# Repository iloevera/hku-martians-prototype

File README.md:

# HKU Martians Prototype Rover

Rudimentary 2-layer all-in-one Power Distribution Board (PDB) and logic carrier designed for small 6-wheel rovers with a 4-DoF robotic arm.

## 🚀 Key Specifications
- **Dimensions:** 99.57 x 99.06 mm
- **Power Input:** 6S LiPo (22.2V nominal, 25.2V max) via XT60.
- **Power Tree:**
  - **12V @ 10.8A:** High-current rail for BLDC/DC Main Drive motors. External module attached through XT30 connectors
  - **7.5V @ 5A:** Dedicated HV Servo rail (Optimized for 7.4V nominal servos). External module attached through XT30 connectors
  - **5.1V @ 5A:** On-board stabilized logic power for Pi 5 and peripherals. 3V3 Using Pico's built-in regulator.
- **Processing:**
  - Dual-core architecture: Raspberry Pi 5 (Thinking) + Pi Pico 2 (Doing).
  - UART communication bridge.
- **Actuation & Sensing:**
  - 6x PWM Encoder inputs.
  - 6x PWM-Controlled DC motor driver headers.
  - 4x High-Torque Servo ports with localized bulk capacitance.
  - Integrated 6S Battery Fuel Gauge (Voltage Divider + ADC).

## 🛠 Hardware Setup
### Battery Monitor Calibration
The internal voltage divider uses a **100kΩ (Top)** and **13.7kΩ (Bottom)** 1% precision resistor set. 
- **Max Input:** 25.2V
- **ADC Output:** ~3.03V
- **Safety Factor:** 10% headroom to prevent Pico ADC overvoltage.

### Communication
The Pi 5 and Pico 2 communicate via UART.
- **Baud Rate:** 115200 (Default)
- **Pinout:** Pi GPIO 14/15 <-> Pico GPIO 0/1.

## ⚠️ Assembly Warnings
1. **Thermal Reliefs:** High-current pads (XT60, Regulators, Motors) have thermal reliefs **DISABLED**. Use a high-power chisel-tip iron and pre-heat the board to 100°C for assembly.
2. **Capacitors:** Ensure C1 & C2 (2000uF) is rated for 50V minimum.
3. **USB Isolation:** Always use a USB isolator when debugging the Pi/Pico while the main battery is connected to prevent back-powering your PC.

## 📜 License
This project is released under CERN-OHL-W-2.0 license. Designed by **Ilo Japar / HKU Martians**.

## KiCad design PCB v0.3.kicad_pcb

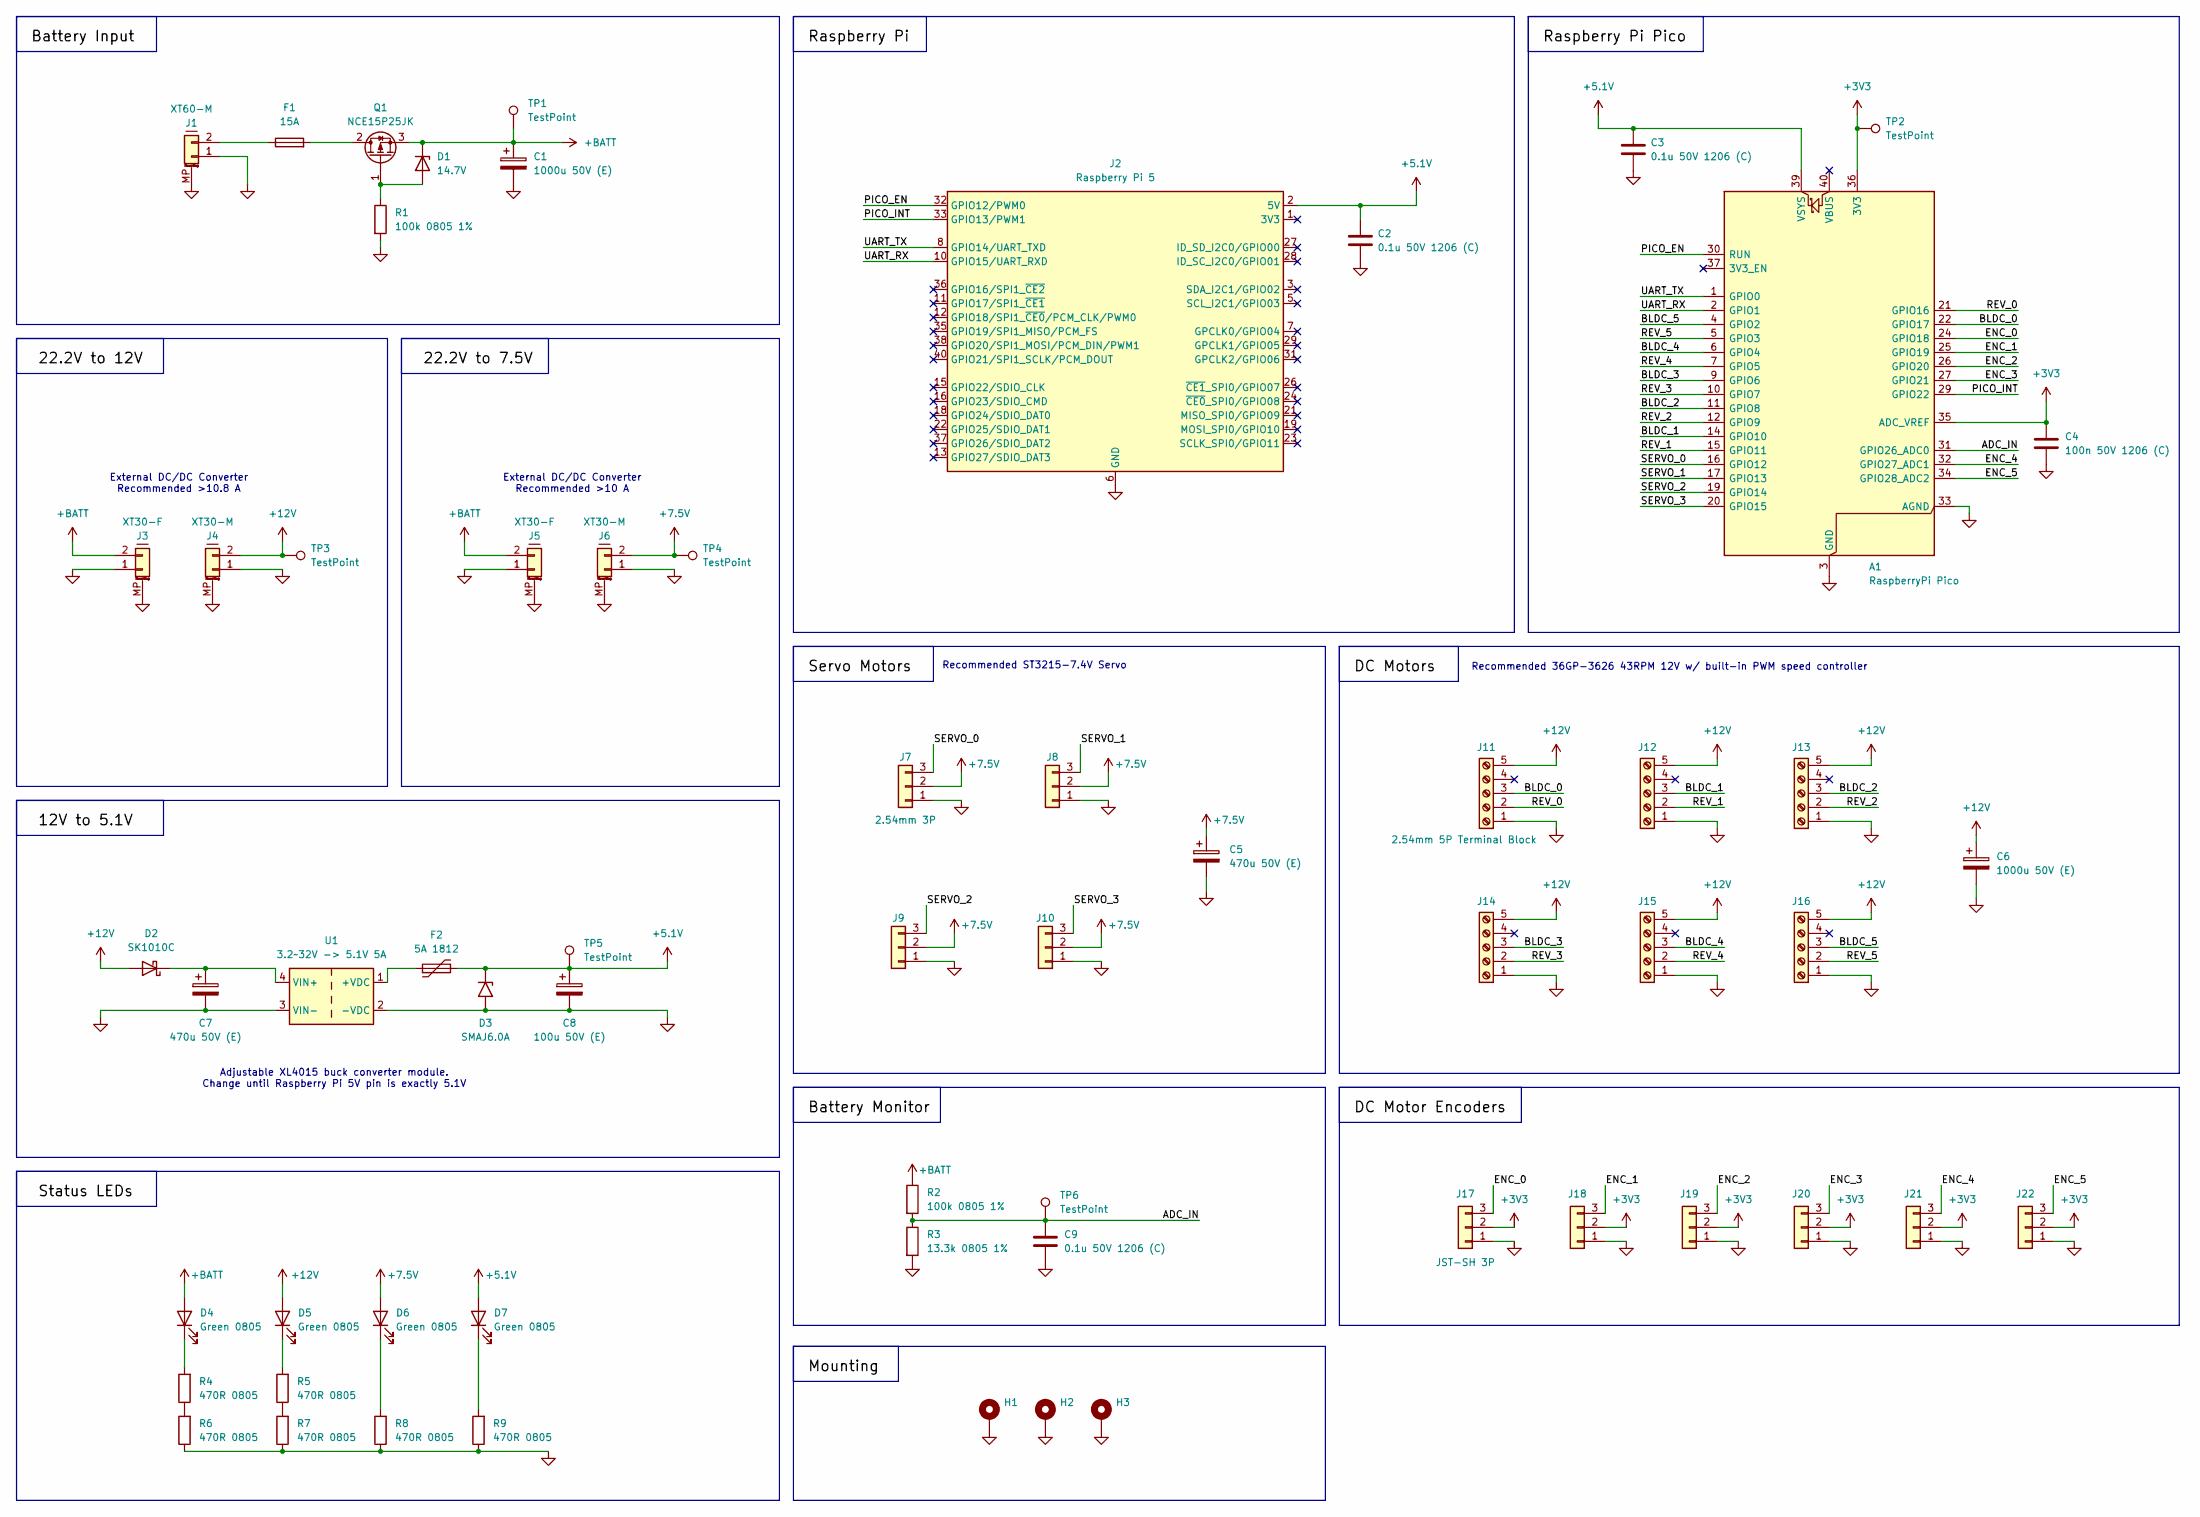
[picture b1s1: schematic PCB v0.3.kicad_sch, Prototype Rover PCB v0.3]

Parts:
A1: RaspberryPi Pico; RaspberryPi_Pico_SMD_HandSolder
C1, C6: 1000u 50V (E); CP_Radial_D13.0mm_P5.00mm
C2, C3, C9: 0.1u 50V 1206 (C); C_1206_3216Metric_Pad1.33x1.80mm_HandSolder
C4: 100n 50V 1206 (C); C_1206_3216Metric_Pad1.33x1.80mm_HandSolder
C5, C7: 470u 50V (E); CP_Radial_D10.0mm_P5.00mm
C8: 100u 50V (E); CP_Radial_D8.0mm_P3.50mm
D1: 14.7V; Nexperia_CFP3_SOD-123W
D2: SK1010C; D_SMC_Handsoldering
D3: SMAJ6.0A; D_SMA
D4, D5, D6, D7: Green 0805; LED_0805_2012Metric_Pad1.15x1.40mm_HandSolder
F1: 15A; Fuse_Blade_ATO_directSolder
F2: 5A 1812; Fuse_1812_4532Metric_Pad1.30x3.40mm_HandSolder
H1, H2, H3: M3 3.2mm; MountingHole_3.2mm_M3_DIN965_Pad
J1: XT60-M; AMASS_XT60PW-M_1x02_P7.20mm_Horizontal
J2: Raspberry Pi 5; raspberrypi_2_3
J3, J5: XT30-F; AMASS_XT30PW-F_1x02_P2.50mm_Horizontal
J4, J6: XT30-M; AMASS_XT30PW-M_1x02_P2.50mm_Horizontal
J7, J8, J9, J10: 2.54mm 3P; PinHeader_1x03_P2.54mm_Vertical
J11, J12, J13, J14, J15, J16: 2.54mm 5P Terminal Block; TerminalBlock_Xinya_XY308-2.54-5P_1x05_P2.54mm_Horizontal
J17, J18, J19, J20, J21, J22: JST-SH 3P; JST_SH_BM03B-SRSS-TB_1x03-1MP_P1.00mm_Vertical
Q1: NCE15P25JK; TO-252-2
R1, R2: 100k 0805 1%; R_0805_2012Metric_Pad1.20x1.40mm_HandSolder
R3: 13.3k 0805 1%; R_0805_2012Metric_Pad1.20x1.40mm_HandSolder
R4, R5, R6, R7, R8, R9: 470R 0805; R_0805_2012Metric_Pad1.20x1.40mm_HandSolder
TP1, TP2, TP3, TP4, TP5, TP6: TestPoint; TestPoint_Pad_D1.5mm
U1: 3.2~32V -> 5.1V 5A; Buck_Converter_54x24mm

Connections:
+3V3: A1.35 (ADC_VREF), A1.36 (3V3), C4.1, J17.2, J18.2, J19.2, J20.2, J21.2, J22.2, TP2.1 (1_1)
+5.1V: A1.39 (VSYS), C2.1, C3.1, C8.1, D3.1 (A1), D7.2 (A), F2.2, J2.2 (5V), J2.4 (5V), TP5.1 (1_1)
+7.5V: C5.1, D6.2 (A), J6.2, J7.2, J8.2, J9.2, J10.2, TP4.1 (1_1)
+12V: C6.1, D2.2 (A), D5.2 (A), J4.2, J11.5, J12.5, J13.5, J14.5, J15.5, J16.5, TP3.1 (1_1)
+BATT: C1.1, D1.1 (K), D4.2 (A), J3.2, J5.2, Q1.3 (S), R2.1, TP1.1 (1_1)
/ADC_IN: A1.31 (GPIO26_ADC0), C9.1, R2.2, R3.1, TP6.1 (1_1)
/BLDC_0: A1.22 (GPIO17), J11.3
/BLDC_1: A1.14 (GPIO10), J12.3
/BLDC_2: A1.11 (GPIO8), J13.3
/BLDC_3: A1.9 (GPIO6), J14.3
/BLDC_4: A1.6 (GPIO4), J15.3
/BLDC_5: A1.4 (GPIO2), J16.3
/ENC_0: A1.24 (GPIO18), J17.3
/ENC_1: A1.25 (GPIO19), J18.3
/ENC_2: A1.26 (GPIO20), J19.3
/ENC_3: A1.27 (GPIO21), J20.3
/ENC_4: A1.32 (GPIO27_ADC1), J21.3
/ENC_5: A1.34 (GPIO28_ADC2), J22.3
/PICO_EN: A1.30 (RUN), J2.32 (GPIO12/PWM0)
/PICO_INT: A1.29 (GPIO22), J2.33 (GPIO13/PWM1)
/REV_0: A1.21 (GPIO16), J11.2
/REV_1: A1.15 (GPIO11), J12.2
/REV_2: A1.12 (GPIO9), J13.2
/REV_3: A1.10 (GPIO7), J14.2
/REV_4: A1.7 (GPIO5), J15.2
/REV_5: A1.5 (GPIO3), J16.2
/SERVO_0: A1.16 (GPIO12), J7.3
/SERVO_1: A1.17 (GPIO13), J8.3
/SERVO_2: A1.19 (GPIO14), J9.3
/SERVO_3: A1.20 (GPIO15), J10.3
/UART_RX: A1.2 (GPIO1), J2.10 (GPIO15/UART_RXD)
/UART_TX: A1.1 (GPIO0), J2.8 (GPIO14/UART_TXD)
GND: A1.3 (GND), A1.8 (GND), A1.13 (GND), A1.18 (GND), A1.23 (GND), A1.28 (GND), A1.33 (AGND), A1.38 (GND), C1.2, C2.2, C3.2, C4.2, C5.2, C6.2, C7.2, C8.2, C9.2, D3.2 (A2), H1.1 (1_1), H2.1 (1_1), H3.1 (1_1), J1.1, J1.MP (MountPin), J2.6 (GND), J2.9 (GND), J2.14 (GND), J2.20 (GND), J2.25 (GND), J2.30 (GND), J2.34 (GND), J2.39 (GND), J3.1, J3.MP (MountPin), J4.1, J4.MP (MountPin), J5.1, J5.MP (MountPin), J6.1, J6.MP (MountPin), J7.1, J8.1, J9.1, J10.1, J11.1, J12.1, J13.1, J14.1, J15.1, J16.1, J17.1, J18.1, J19.1, J20.1, J21.1, J22.1, R1.2, R3.2, R6.1, R7.1, R8.1, R9.1, U1.2 (-VDC), U1.3 (VIN-)
unnamed: D1.2 (A), Q1.1 (G), R1.1
unnamed: C7.1, D2.1 (K), U1.4 (VIN+)
unnamed: D4.1 (K), R4.2
unnamed: D5.1 (K), R5.2
unnamed: D6.1 (K), R8.2
unnamed: D7.1 (K), R9.2
unnamed: F1.1, J1.2
unnamed: F1.2, Q1.2 (D)
unnamed: R4.1, R6.2
unnamed: R5.1, R7.2
unnamed: F2.1, U1.1 (+VDC)

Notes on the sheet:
Adjustable XL4015 buck converter module. Change until Raspberry Pi 5V pin is exactly 5.1V
External DC/DC Converter Recommended >10 A
Recommended 36GP-3626 43RPM 12V w/ built-in PWM speed controller
Recommended ST3215-7.4V Servo
External DC/DC Converter Recommended >10.8 A

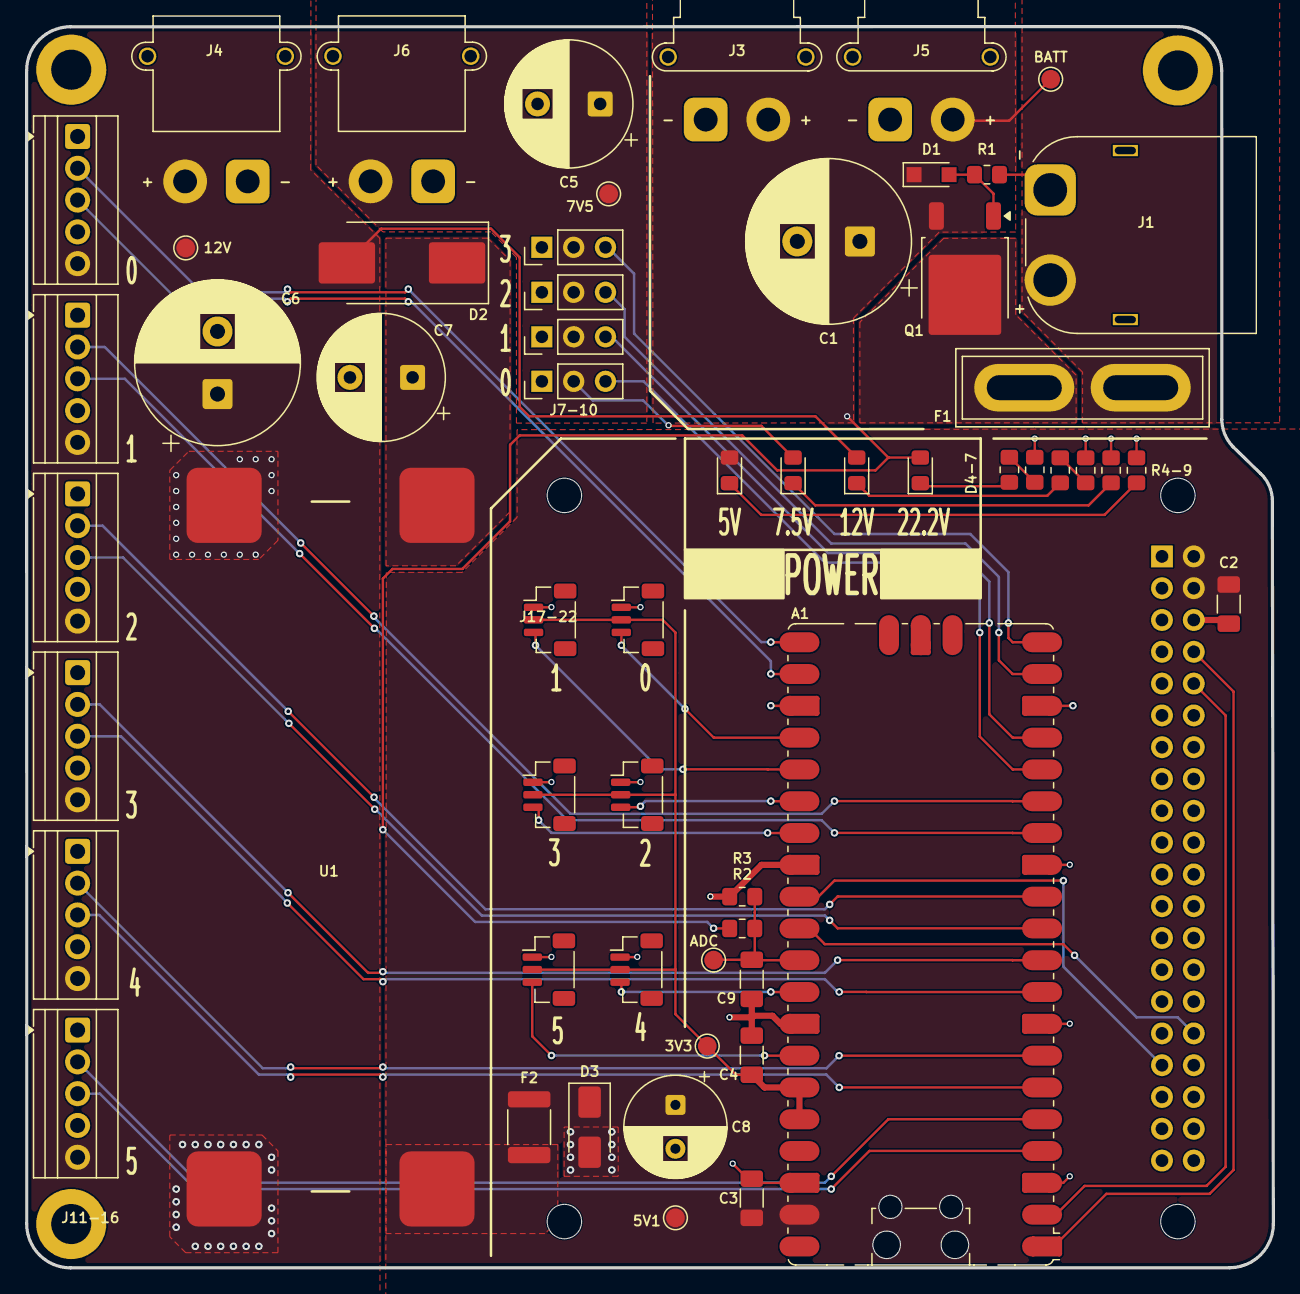
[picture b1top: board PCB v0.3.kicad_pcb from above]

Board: 2 copper layers, 99.6 x 99.1 mm, 61 parts (0 on the bottom side), 44 nets.

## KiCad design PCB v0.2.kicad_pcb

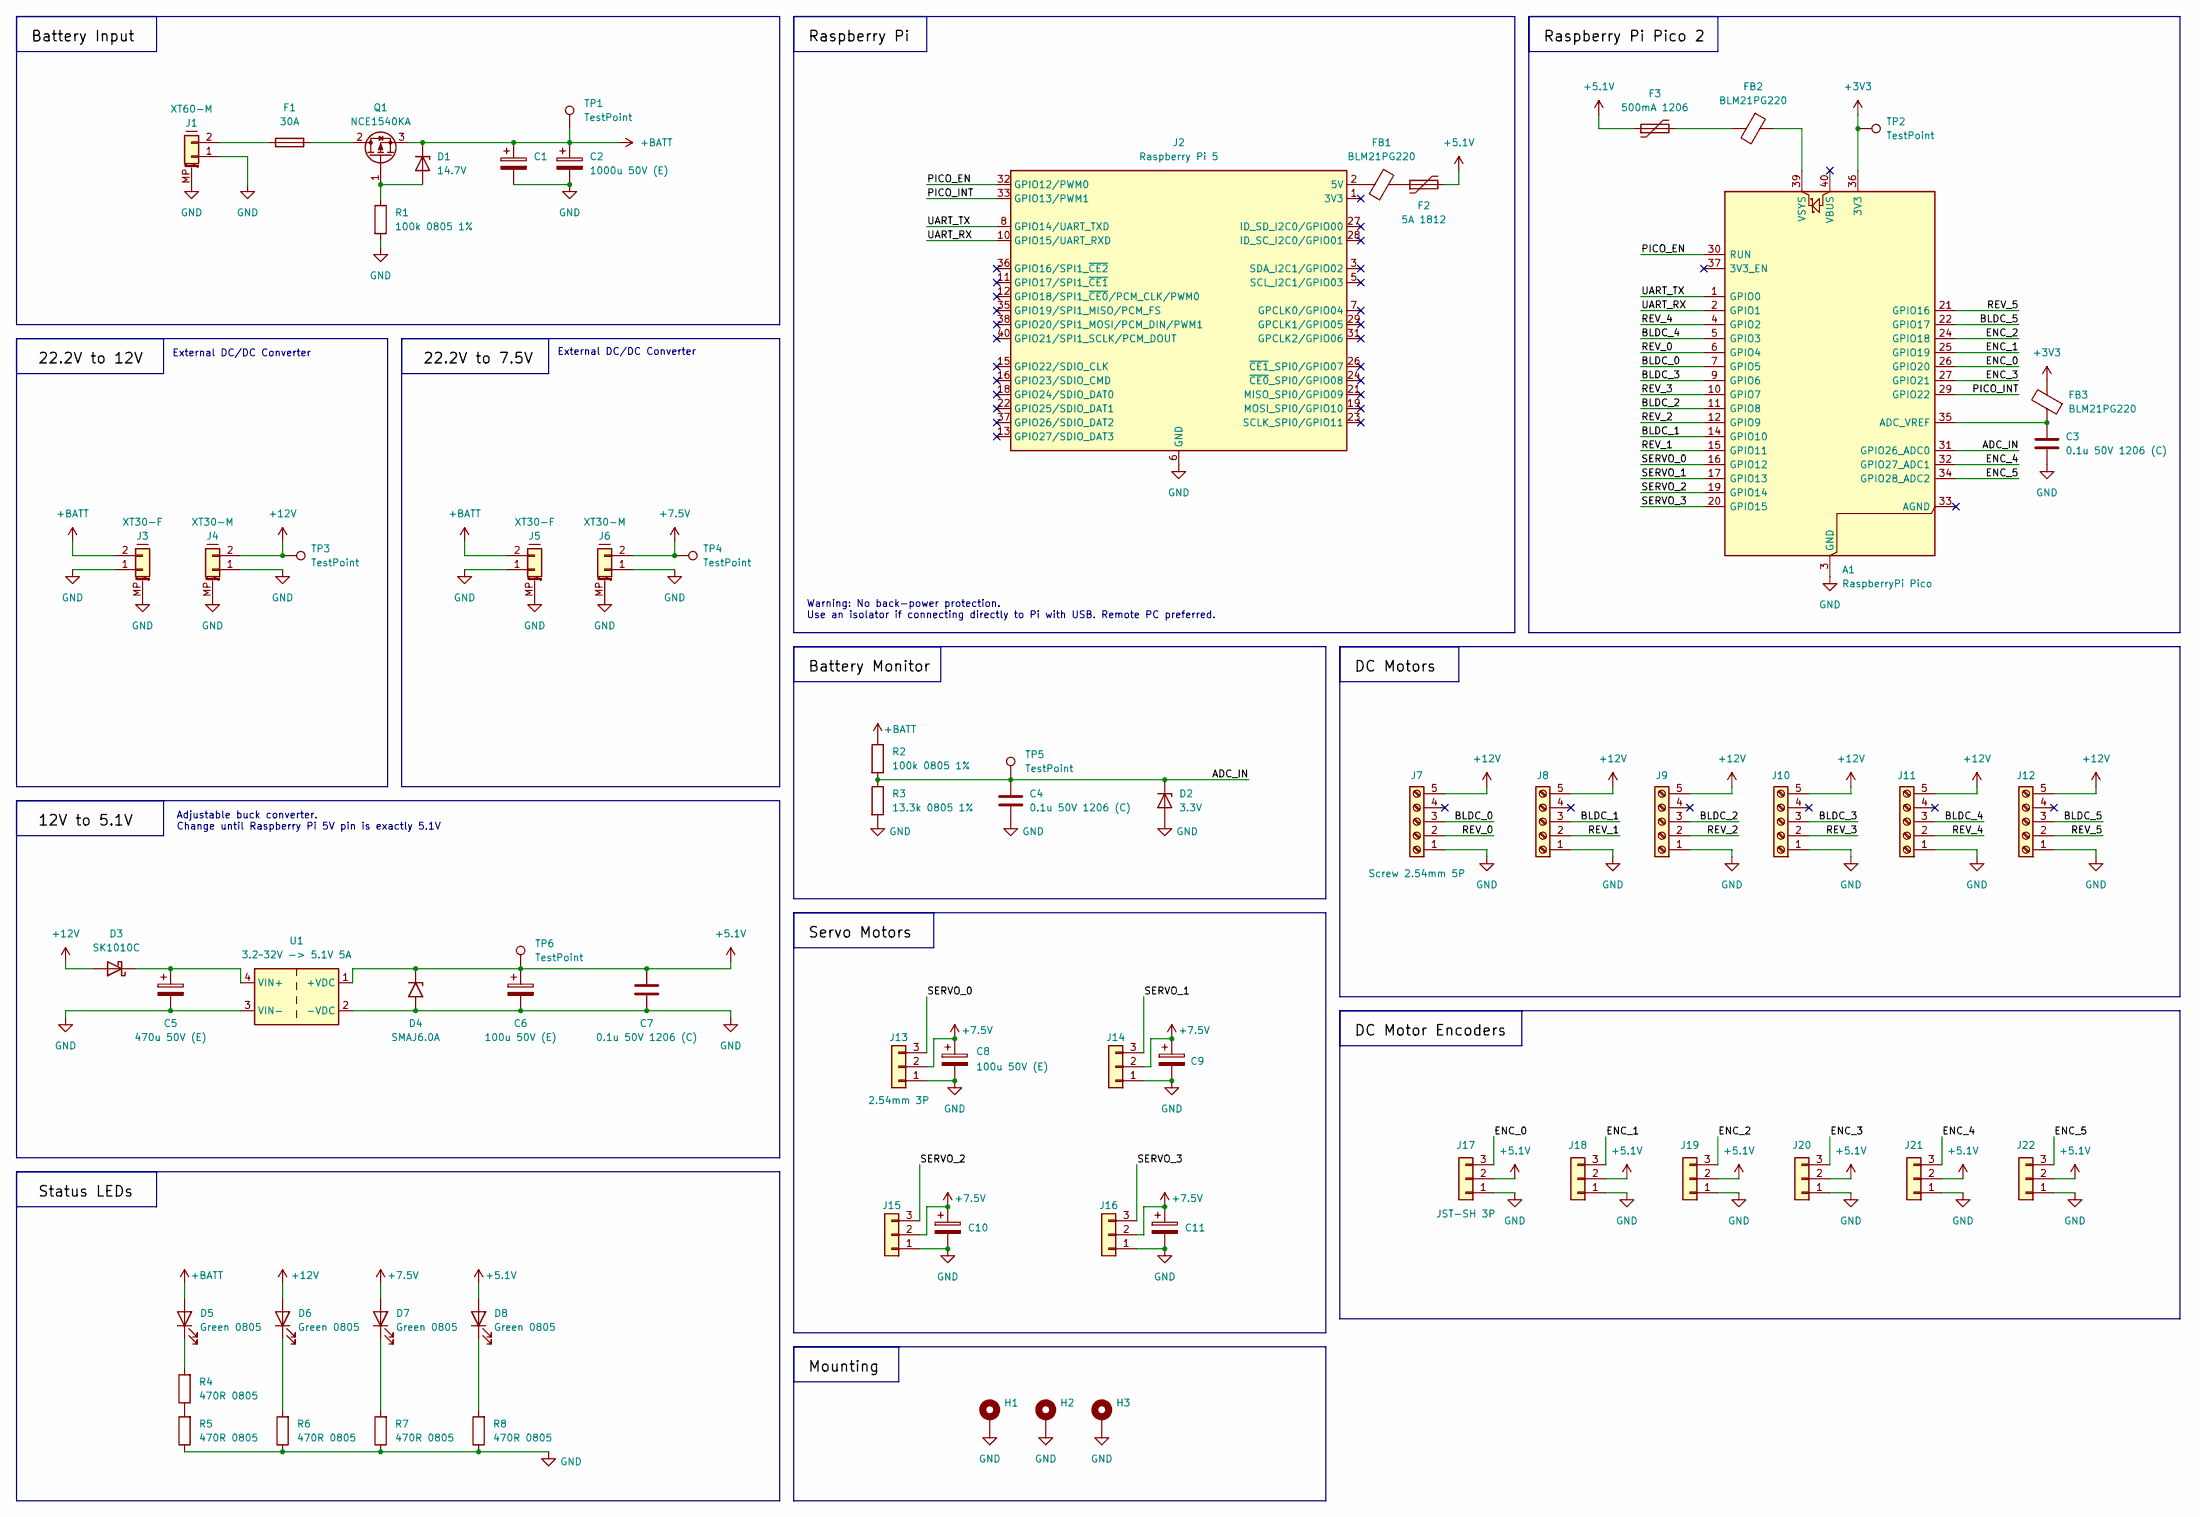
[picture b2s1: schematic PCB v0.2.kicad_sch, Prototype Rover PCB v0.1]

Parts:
A1: RaspberryPi Pico; RaspberryPi_Pico_SMD_HandSolder
C1, C2: 1000u 50V (E); CP_Radial_D13.0mm_P5.00mm
C3, C4, C7: 0.1u 50V 1206 (C); C_1206_3216Metric_Pad1.33x1.80mm_HandSolder
C5: 470u 50V (E); CP_Radial_D10.0mm_P5.00mm
C6, C8, C9, C10, C11: 100u 50V (E); CP_Radial_D8.0mm_P3.50mm
D1: 14.7V; Nexperia_CFP3_SOD-123W
D2: 3.3V; Nexperia_CFP3_SOD-123W
D3: SK1010C; D_SMC_Handsoldering
D4: SMAJ6.0A; D_SMA
D5, D6, D7, D8: Green 0805; LED_0805_2012Metric_Pad1.15x1.40mm_HandSolder
F1: 30A; FuseHolder_Blade_ATO_Littelfuse_FLR_178.6165
F2: 5A 1812; Fuse_1206_3216Metric
F3: 500mA 1206; Fuse_1206_3216Metric
FB1, FB2, FB3: BLM21PG220; L_0805_2012Metric_Pad1.05x1.20mm_HandSolder
H1, H2, H3: M3 3.2mm; MountingHole_3.2mm_M3_DIN965_Pad
J1: XT60-M; AMASS_XT60PW-M_1x02_P7.20mm_Horizontal
J2: Raspberry Pi 5; Raspberry_Pi_5
J3, J5: XT30-F; AMASS_XT30PW-F_1x02_P2.50mm_Horizontal
J4, J6: XT30-M; AMASS_XT30PW-M_1x02_P2.50mm_Horizontal
J7, J8, J9, J10, J11, J12: Screw 2.54mm 5P; TerminalBlock_Xinya_XY308-2.54-5P_1x05_P2.54mm_Horizontal
J13, J14, J15, J16: 2.54mm 3P; PinHeader_1x03_P2.54mm_Vertical
J17, J18, J19, J20, J21, J22: JST-SH 3P; JST_SH_BM03B-SRSS-TB_1x03-1MP_P1.00mm_Vertical
Q1: NCE1540KA; TO-252-2
R1, R2: 100k 0805 1%; R_0805_2012Metric_Pad1.20x1.40mm_HandSolder
R3: 13.3k 0805 1%; R_0805_2012Metric_Pad1.20x1.40mm_HandSolder
R4, R5, R6, R7, R8: 470R 0805; R_0805_2012Metric_Pad1.20x1.40mm_HandSolder
TP1, TP2, TP3, TP4, TP5, TP6: TestPoint; TestPoint_Pad_D1.5mm
U1: 3.2~32V -> 5.1V 5A; Buck_Converter_54x24mm

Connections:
+3V3: A1.36 (3V3), FB3.2, TP2.1 (1_1)
+5.1V: C6.1, C7.1, D4.1 (A1), D8.2 (A), F2.2, F3.1, J17.2, J18.2, J19.2, J20.2, J21.2, J22.2, TP6.1 (1_1), U1.1 (+VDC)
+7.5V: C8.1, C9.1, C10.1, C11.1, D7.2 (A), J6.2, J13.2, J14.2, J15.2, J16.2, TP4.1 (1_1)
+12V: D3.2 (A), D6.2 (A), J4.2, J7.5, J8.5, J9.5, J10.5, J11.5, J12.5, TP3.1 (1_1)
+BATT: C1.1, C2.1, D1.1 (K), D5.2 (A), J3.2, J5.2, Q1.3 (S), R2.1, TP1.1 (1_1)
/ADC_IN: A1.31 (GPIO26_ADC0), C4.1, D2.1 (K), R2.2, R3.1, TP5.1 (1_1)
/BLDC_0: A1.7 (GPIO5), J7.3
/BLDC_1: A1.14 (GPIO10), J8.3
/BLDC_2: A1.11 (GPIO8), J9.3
/BLDC_3: A1.9 (GPIO6), J10.3
/BLDC_4: A1.5 (GPIO3), J11.3
/BLDC_5: A1.22 (GPIO17), J12.3
/ENC_0: A1.26 (GPIO20), J17.3
/ENC_1: A1.25 (GPIO19), J18.3
/ENC_2: A1.24 (GPIO18), J19.3
/ENC_3: A1.27 (GPIO21), J20.3
/ENC_4: A1.32 (GPIO27_ADC1), J21.3
/ENC_5: A1.34 (GPIO28_ADC2), J22.3
/PICO_EN: A1.30 (RUN), J2.32 (GPIO12/PWM0)
/PICO_INT: A1.29 (GPIO22), J2.33 (GPIO13/PWM1)
/REV_0: A1.6 (GPIO4), J7.2
/REV_1: A1.15 (GPIO11), J8.2
/REV_2: A1.12 (GPIO9), J9.2
/REV_3: A1.10 (GPIO7), J10.2
/REV_4: A1.4 (GPIO2), J11.2
/REV_5: A1.21 (GPIO16), J12.2
/SERVO_0: A1.16 (GPIO12), J13.3
/SERVO_1: A1.17 (GPIO13), J14.3
/SERVO_2: A1.19 (GPIO14), J15.3
/SERVO_3: A1.20 (GPIO15), J16.3
/UART_RX: A1.2 (GPIO1), J2.10 (GPIO15/UART_RXD)
/UART_TX: A1.1 (GPIO0), J2.8 (GPIO14/UART_TXD)
GND: A1.3 (GND), A1.8 (GND), A1.13 (GND), A1.18 (GND), A1.23 (GND), A1.28 (GND), A1.38 (GND), C1.2, C2.2, C3.2, C4.2, C5.2, C6.2, C7.2, C8.2, C9.2, C10.2, C11.2, D2.2 (A), D4.2 (A2), H1.1 (1_1), H2.1 (1_1), H3.1 (1_1), J1.1, J1.MP (MountPin), J2.6 (GND), J2.9 (GND), J2.14 (GND), J2.20 (GND), J2.25 (GND), J2.30 (GND), J2.34 (GND), J2.39 (GND), J3.1, J3.MP (MountPin), J4.1, J4.MP (MountPin), J5.1, J5.MP (MountPin), J6.1, J6.MP (MountPin), J7.1, J8.1, J9.1, J10.1, J11.1, J12.1, J13.1, J14.1, J15.1, J16.1, J17.1, J18.1, J19.1, J20.1, J21.1, J22.1, R1.2, R3.2, R5.1, R6.1, R7.1, R8.1, U1.2 (-VDC), U1.3 (VIN-)
unnamed: A1.35 (ADC_VREF), C3.1, FB3.1
unnamed: A1.39 (VSYS), FB2.1
unnamed: D1.2 (A), Q1.1 (G), R1.1
unnamed: C5.1, D3.1 (K), U1.4 (VIN+)
unnamed: D5.1 (K), R4.2
unnamed: D6.1 (K), R6.2
unnamed: D7.1 (K), R7.2
unnamed: D8.1 (K), R8.2
unnamed: F2.1, FB1.2
unnamed: F3.2, FB2.2
unnamed: FB1.1, J2.2 (5V), J2.4 (5V)
unnamed: F1.1, J1.2
unnamed: F1.2, Q1.2 (D)
unnamed: R4.1, R5.2

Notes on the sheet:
Warning: No back-power protection. Use an isolator if connecting directly to Pi with USB. Remote PC preferred.
Adjustable buck converter. Change until Raspberry Pi 5V pin is exactly 5.1V
External DC/DC Converter

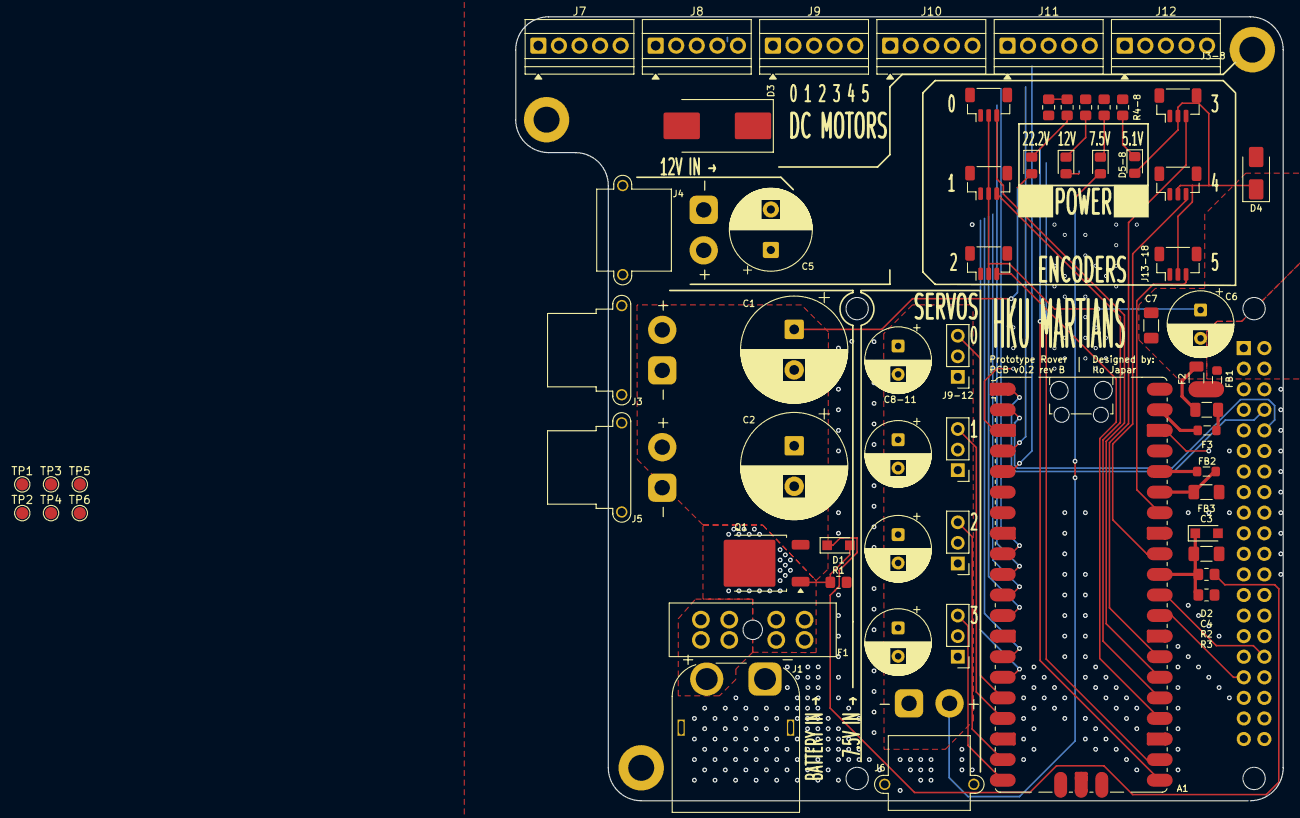
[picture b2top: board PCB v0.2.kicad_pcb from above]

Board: 2 copper layers, 94.7 x 96.8 mm, 67 parts (1 on the bottom side), 47 nets.

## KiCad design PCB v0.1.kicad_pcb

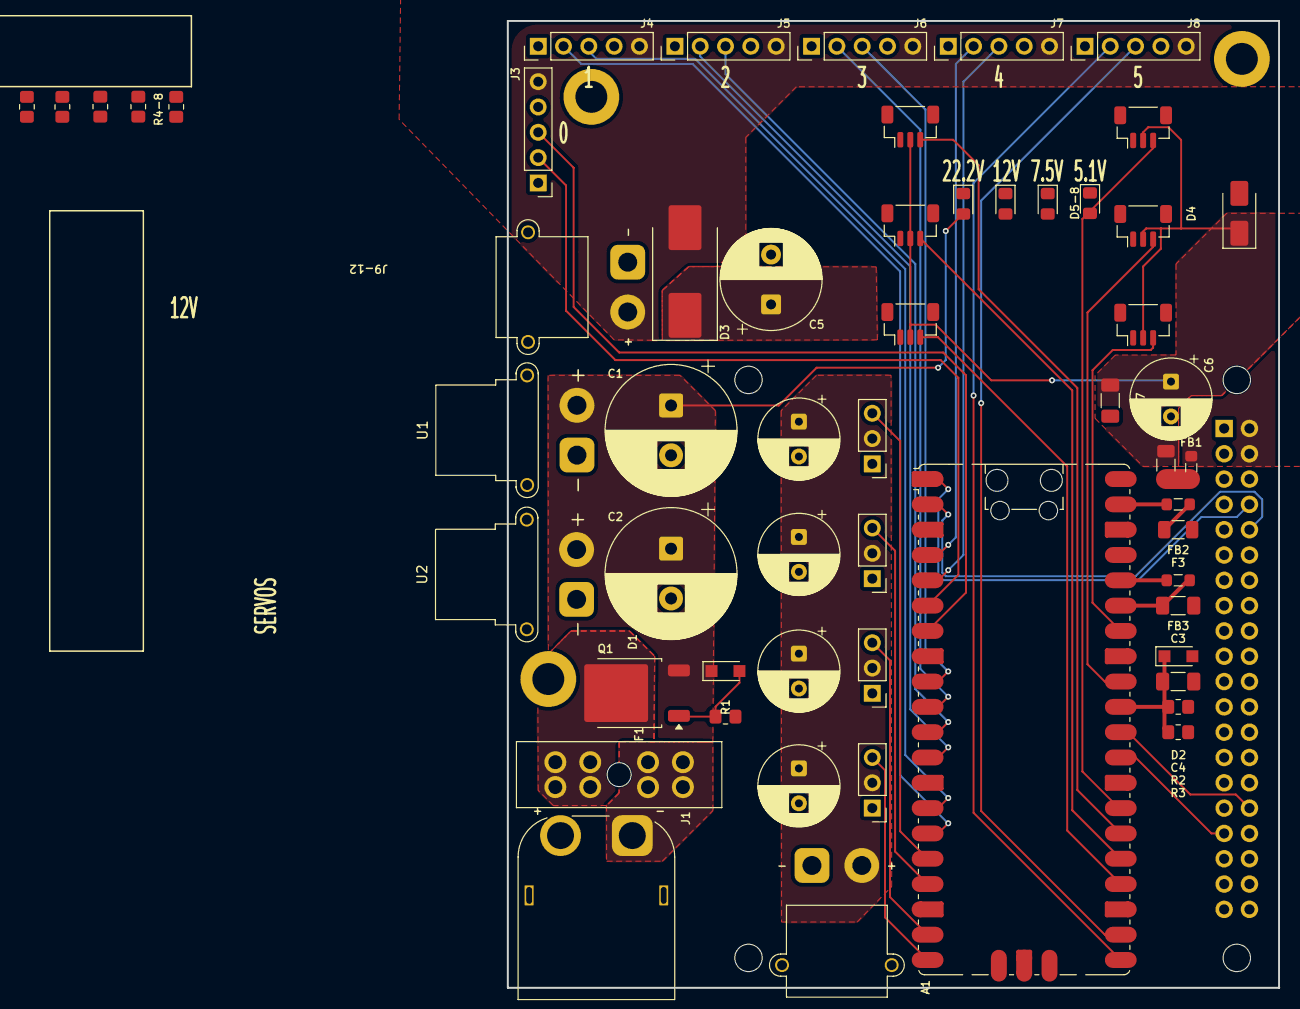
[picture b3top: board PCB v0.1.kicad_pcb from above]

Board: 2 copper layers, 77.4 x 97.0 mm, 61 parts (1 on the bottom side), 47 nets.

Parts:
A1: RaspberryPi Pico; RaspberryPi_Pico_SMD_HandSolder
C1, C2: 1000u 50V (E); CP_Radial_D13.0mm_P5.00mm
C3, C4, C7: 0.1u 50V 1206 (C); C_1206_3216Metric_Pad1.33x1.80mm_HandSolder
C5: 470u 50V (E); CP_Radial_D10.0mm_P5.00mm
C6, C8, C9, C10, C11: 100u 50V (E); CP_Radial_D8.0mm_P3.50mm
D1: 14.7V; Nexperia_CFP3_SOD-123W
D2: 3.3V; Nexperia_CFP3_SOD-123W
D3: SK1010C; D_SMC_Handsoldering
D4: SMAJ6.0A; D_SMA
D5, D6, D7, D8: Green 0805; LED_0805_2012Metric_Pad1.15x1.40mm_HandSolder
F1: 30A; FuseHolder_Blade_ATO_Littelfuse_FLR_178.6165
F2: 5A 1812; Fuse_1206_3216Metric
F3: 500mA 1206; Fuse_1206_3216Metric
FB1, FB2, FB3: BLM21PG220; L_0805_2012Metric_Pad1.05x1.20mm_HandSolder
H1, H2, H3: M3 3.2mm; MountingHole_3.2mm_M3_DIN965_Pad
J1: XT60 M (Vertical); AMASS_XT60PW-M_1x02_P7.20mm_Horizontal
J2: Raspberry Pi 5; Raspberry_Pi_5
J3: Screw 2.54mm 5P; PinHeader_1x05_P2.54mm_Vertical
J4, J5, J6, J7, J8: Screw Terminal 5P; PinHeader_1x05_P2.54mm_Vertical
J9, J10, J11, J12: 2.54mm 3P; PinHeader_1x03_P2.54mm_Vertical
J13, J14, J15, J16, J17, J18: JST-SH 3P; JST_SH_BM03B-SRSS-TB_1x03-1MP_P1.00mm_Vertical
Q1: NCE1540KA; TO-252-2
R1, R2: 100k 0805 1%; R_0805_2012Metric_Pad1.20x1.40mm_HandSolder
R3: 13.3k 0805 1%; R_0805_2012Metric_Pad1.20x1.40mm_HandSolder
R4, R5, R6, R7, R8: 470R 0805; R_0805_2012Metric_Pad1.20x1.40mm_HandSolder
U1, U2: AMASS_XT30PW-F_1x02_P2.50mm_Horizontal
U1#2, U2#2: AMASS_XT30PW-M_1x02_P2.50mm_Horizontal
U3: 3.2~32V -> 5.1V 5A; Buck_Converter_44x22mm

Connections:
+3V3: A1.36 (3V3), FB3.2
+5.1V: C6.1, C7.1, D4.1 (A1), D8.2 (A), F2.2, F3.1, J13.2, J14.2, J15.2, J16.2, J17.2, J18.2, U3.1 (+VDC)
+7.5V: C8.1, C9.1, C10.1, C11.1, D7.2 (A), J9.2, J10.2, J11.2, J12.2, U2#2.1
+12V: D3.2 (A), D6.2 (A), J3.5, J4.5, J5.5, J6.5, J7.5, J8.5, U1#2.1
+BATT: C1.1, C2.1, D1.1 (K), D5.2 (A), Q1.3 (S), R2.1, U1.4, U2.4
/ADC_IN: A1.31 (GPIO26_ADC0), C4.1, D2.1 (K), R2.2, R3.1
/BLDC_0: A1.7 (GPIO5), J3.3
/BLDC_1: A1.14 (GPIO10), J4.3
/BLDC_2: A1.11 (GPIO8), J5.3
/BLDC_3: A1.9 (GPIO6), J6.3
/BLDC_4: A1.5 (GPIO3), J7.3
/BLDC_5: A1.22 (GPIO17), J8.3
/ENC_0: A1.26 (GPIO20), J13.3
/ENC_1: A1.25 (GPIO19), J14.3
/ENC_2: A1.24 (GPIO18), J15.3
/ENC_3: A1.27 (GPIO21), J16.3
/ENC_4: A1.32 (GPIO27_ADC1), J17.3
/ENC_5: A1.34 (GPIO28_ADC2), J18.3
/PICO_EN: A1.30 (RUN), J2.32 (GPIO12/PWM0)
/PICO_INT: A1.29 (GPIO22), J2.33 (GPIO13/PWM1)
/REV_0: A1.6 (GPIO4), J3.2
/REV_1: A1.15 (GPIO11), J4.2
/REV_2: A1.12 (GPIO9), J5.2
/REV_3: A1.10 (GPIO7), J6.2
/REV_4: A1.4 (GPIO2), J7.2
/REV_5: A1.21 (GPIO16), J8.2
/SERVO_0: A1.16 (GPIO12), J9.3
/SERVO_1: A1.17 (GPIO13), J10.3
/SERVO_2: A1.19 (GPIO14), J11.3
/SERVO_3: A1.20 (GPIO15), J12.3
/UART_RX: A1.2 (GPIO1), J2.10 (GPIO15/UART_RXD)
/UART_TX: A1.1 (GPIO0), J2.8 (GPIO14/UART_TXD)
GND: A1.3 (GND), A1.8 (GND), A1.13 (GND), A1.18 (GND), A1.23 (GND), A1.28 (GND), A1.38 (GND), C1.2, C2.2, C3.2, C4.2, C5.2, C6.2, C7.2, C8.2, C9.2, C10.2, C11.2, D2.2 (A), D4.2 (A2), H1.1 (1_1), H2.1 (1_1), H3.1 (1_1), J1.2, J2.6 (GND), J2.9 (GND), J2.14 (GND), J2.20 (GND), J2.25 (GND), J2.30 (GND), J2.34 (GND), J2.39 (GND), J3.1, J4.1, J5.1, J6.1, J7.1, J8.1, J9.1, J10.1, J11.1, J12.1, J13.1, J14.1, J15.1, J16.1, J17.1, J18.1, R1.2, R3.2, R5.1, R6.1, R7.1, R8.1, U1.3, U1#2.2, U2.3, U2#2.2, U3.2 (-VDC), U3.3 (VIN-)
unnamed: A1.35 (ADC_VREF), C3.1, FB3.1
unnamed: A1.39 (VSYS), FB2.1
unnamed: D1.2 (A), Q1.1 (G), R1.1
unnamed: C5.1, D3.1 (K), U3.4 (VIN+)
unnamed: D5.1 (K), R4.2
unnamed: D6.1 (K), R6.2
unnamed: D7.1 (K), R7.2
unnamed: D8.1 (K), R8.2
unnamed: F2.1, FB1.2
unnamed: F3.2, FB2.2
unnamed: FB1.1, J2.2 (5V), J2.4 (5V)
unnamed: F1.1, J1.1
unnamed: F1.2, Q1.2 (D)
unnamed: R4.1, R5.2

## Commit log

2026-04-08 Began adding footprints & datasheets
2026-04-08 Finished design. TODO: Servo actually 7.4V. Needs fix
2026-04-09 Todo: 7.5V buck collides with RPi
2026-04-10 Rev A finished. docs made, BOM made.
2026-04-10 Updated README
    Updated description to specify design for small 6-wheel rovers with a 4-DoF robotic arm.
2026-04-10 Added image and key specifications to the README.
2026-04-10 Change PCB image in README
    Updated PCB image link in README.
2026-04-10 Revise power specifications and remove protection features
    Updated power tree specifications and added details about external module connections. Removed protection features section.
2026-04-10 Rename team from HKU ROVER to HKU Martians
2026-04-11 Created new layout, fixed XT30 polarity
2026-04-11 v0.2. Corrected XT30 polarity, less than 10x10cm in size
2026-04-11 v0.2. Added dimensions. Replaced image
    Updated PCB image link and corrected text formatting.
2026-04-13 U1 symbol was not in v0.2
2026-05-08 Changed PCB
2026-05-08 Finished v0.3 SCH
2026-05-08 Laid out power circuitry
2026-05-08 Finished laying out
2026-05-08 Power planes, began routing
2026-05-09 Finished layout and routing. Begun documentation
2026-05-13 Add documentation and gerbers
2026-05-13 Fix image link and update power tree specifications
    Updated image link and corrected power specifications.
2026-05-13 Update description of Power Distribution Board
